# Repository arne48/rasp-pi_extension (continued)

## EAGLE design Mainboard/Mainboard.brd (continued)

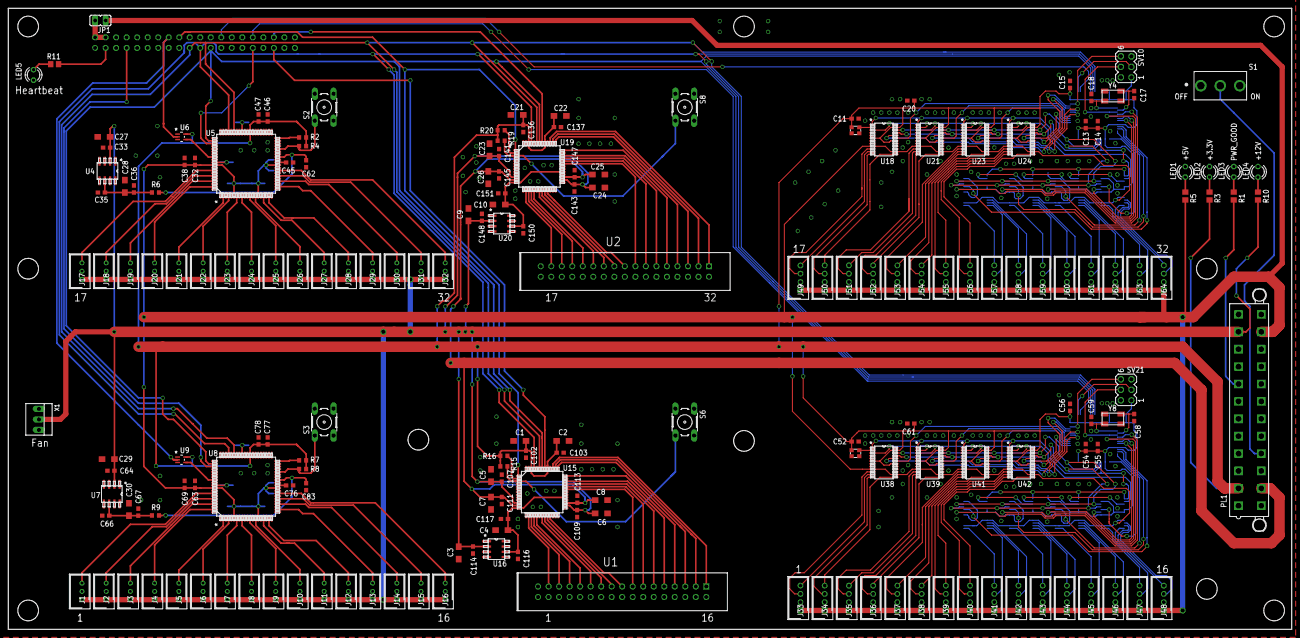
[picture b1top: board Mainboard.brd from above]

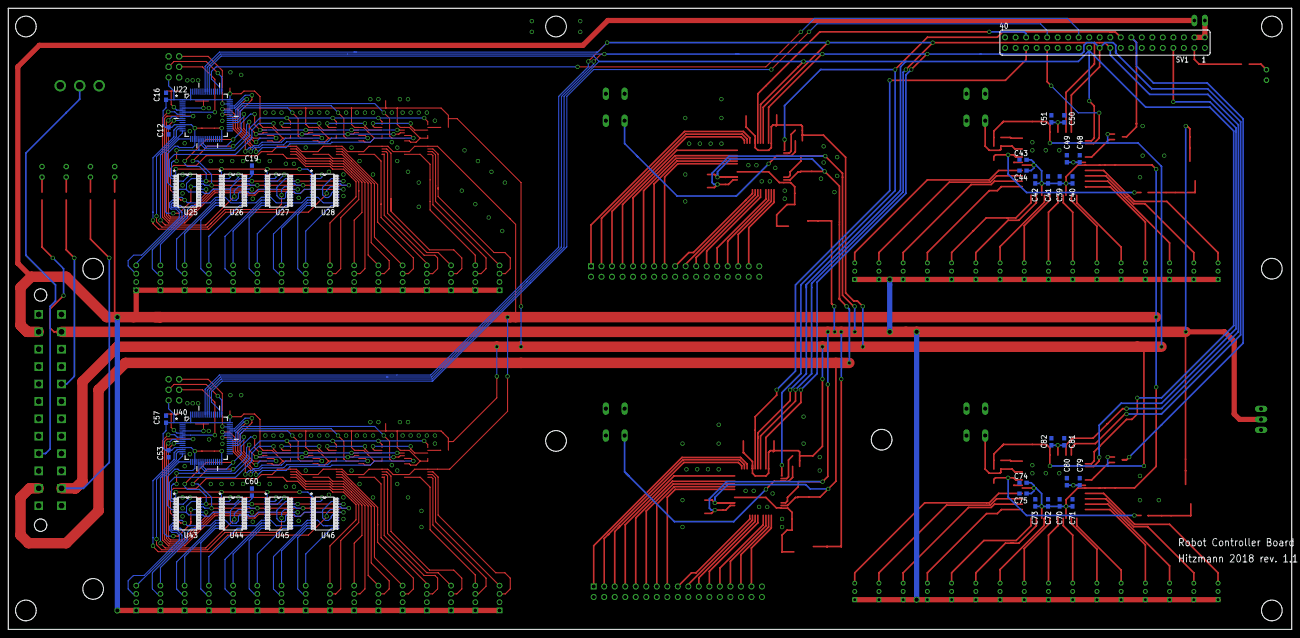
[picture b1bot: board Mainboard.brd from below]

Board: 2 copper layers, 310.0 x 150.0 mm, 225 parts (37 on the bottom side), 240 nets.

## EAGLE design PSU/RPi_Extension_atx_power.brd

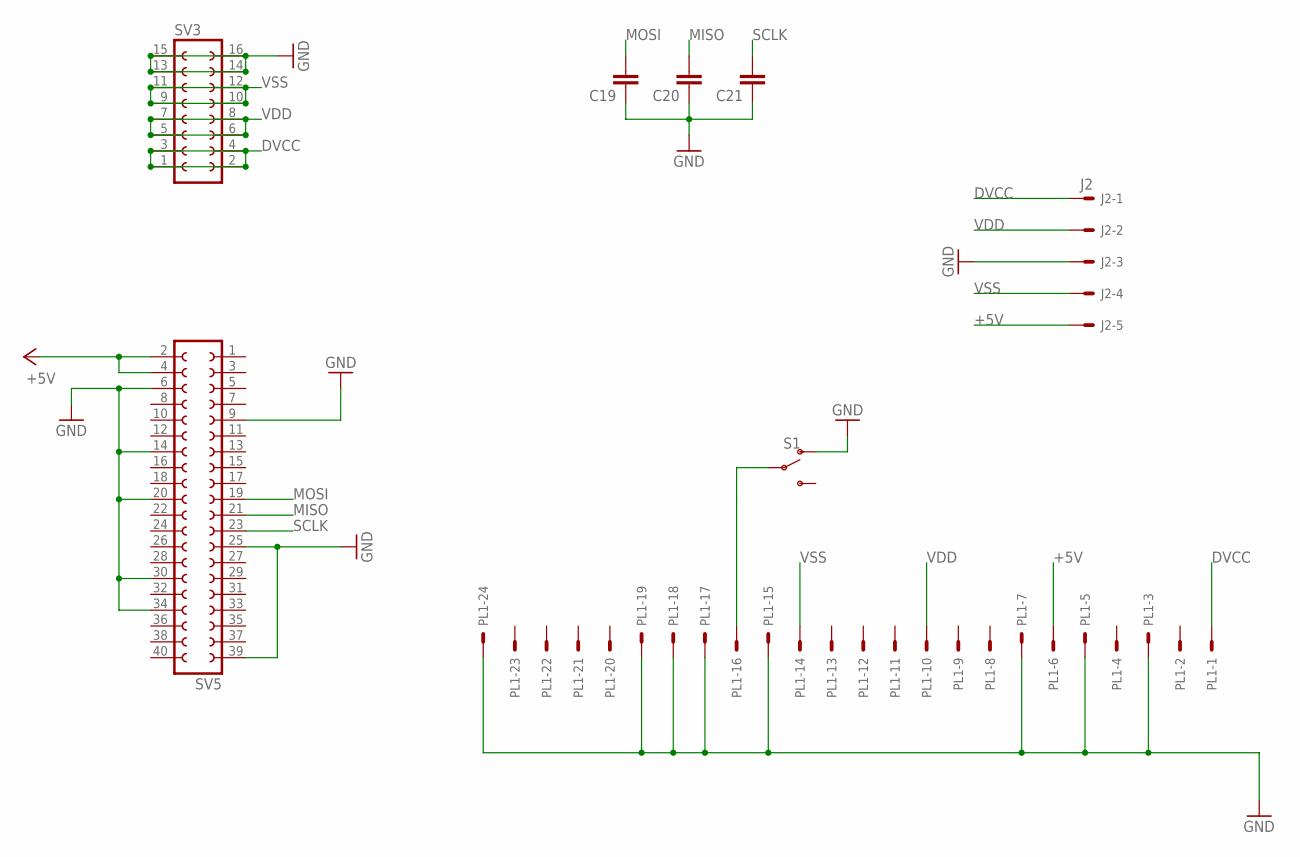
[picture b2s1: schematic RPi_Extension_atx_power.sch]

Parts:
C19, C20, C21: C-EUC0603; C0603
J2: J2; 6410-05
PL1: 555X-24V; 5566-24
S1: SWITCH-SPDT-PTH-11.6X4.0MM; SWITCH_SPDT_PTH_11.6X4.0MM
SV3: FE08-2
SV5: FE20-2

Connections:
+5V: J2.5, PL1.6, SV5.2, SV5.4
DVCC: J2.1, PL1.1, SV3.1, SV3.2, SV3.3, SV3.4
GND: C19.1, C20.1, C21.1, J2.3, PL1.3, PL1.5, PL1.7, PL1.15, PL1.17, PL1.18, PL1.19, PL1.24, S1.1 (O), SV3.13, SV3.14, SV3.15, SV3.16, SV5.6, SV5.9, SV5.14, SV5.20, SV5.25, SV5.30, SV5.34, SV5.39
MISO: C20.2, SV5.21
MOSI: C19.2, SV5.19
unnamed: PL1.16, S1.2
SCLK: C21.2, SV5.23
VDD: J2.2, PL1.10, SV3.5, SV3.6, SV3.7, SV3.8
VSS: J2.4, PL1.14, SV3.9, SV3.10, SV3.11, SV3.12

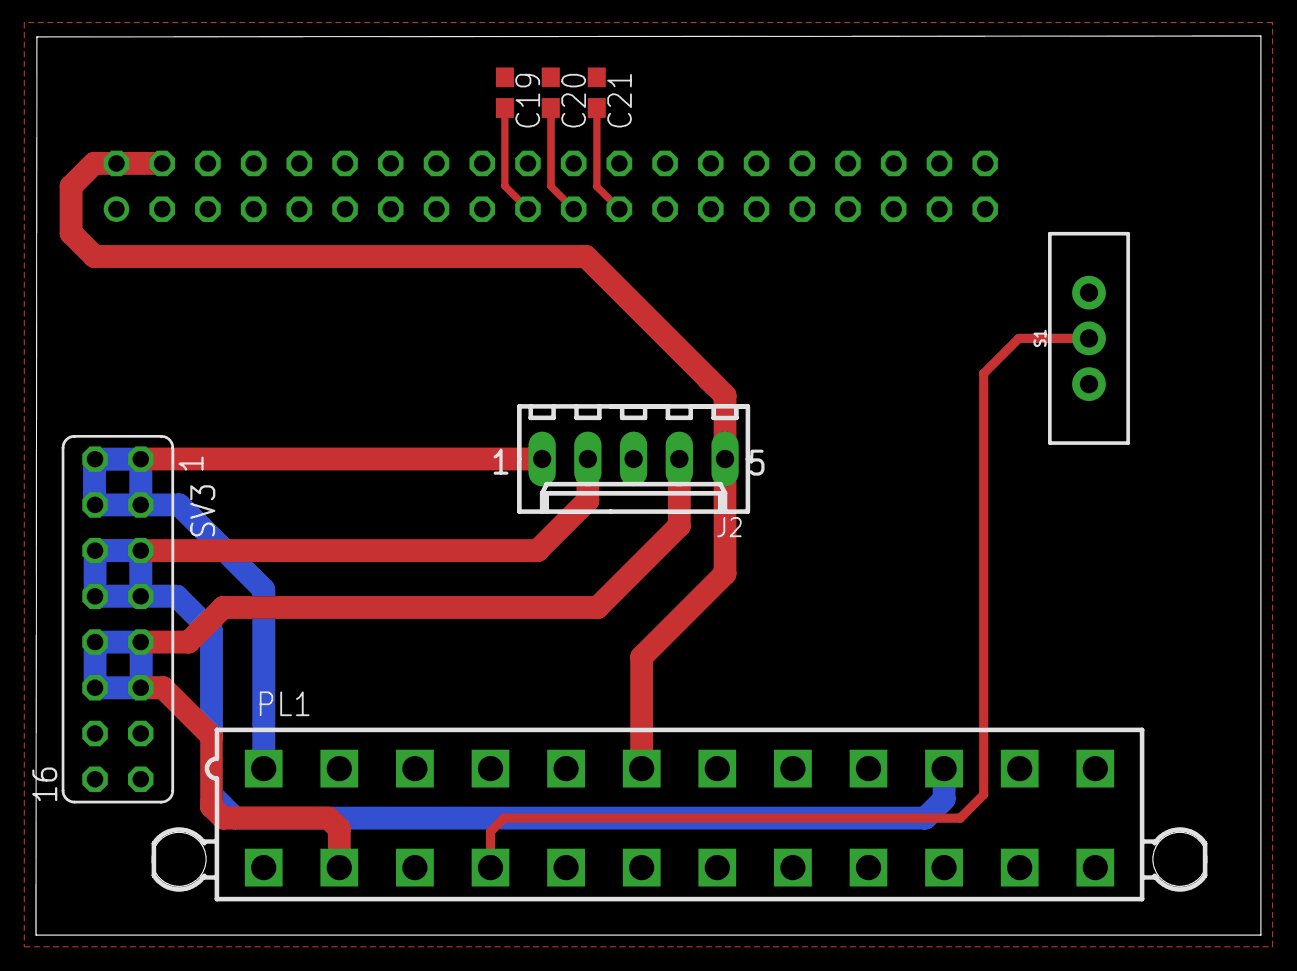
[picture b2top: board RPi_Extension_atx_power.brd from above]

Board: 2 copper layers, 68.0 x 50.0 mm, 8 parts (1 on the bottom side), 9 nets.

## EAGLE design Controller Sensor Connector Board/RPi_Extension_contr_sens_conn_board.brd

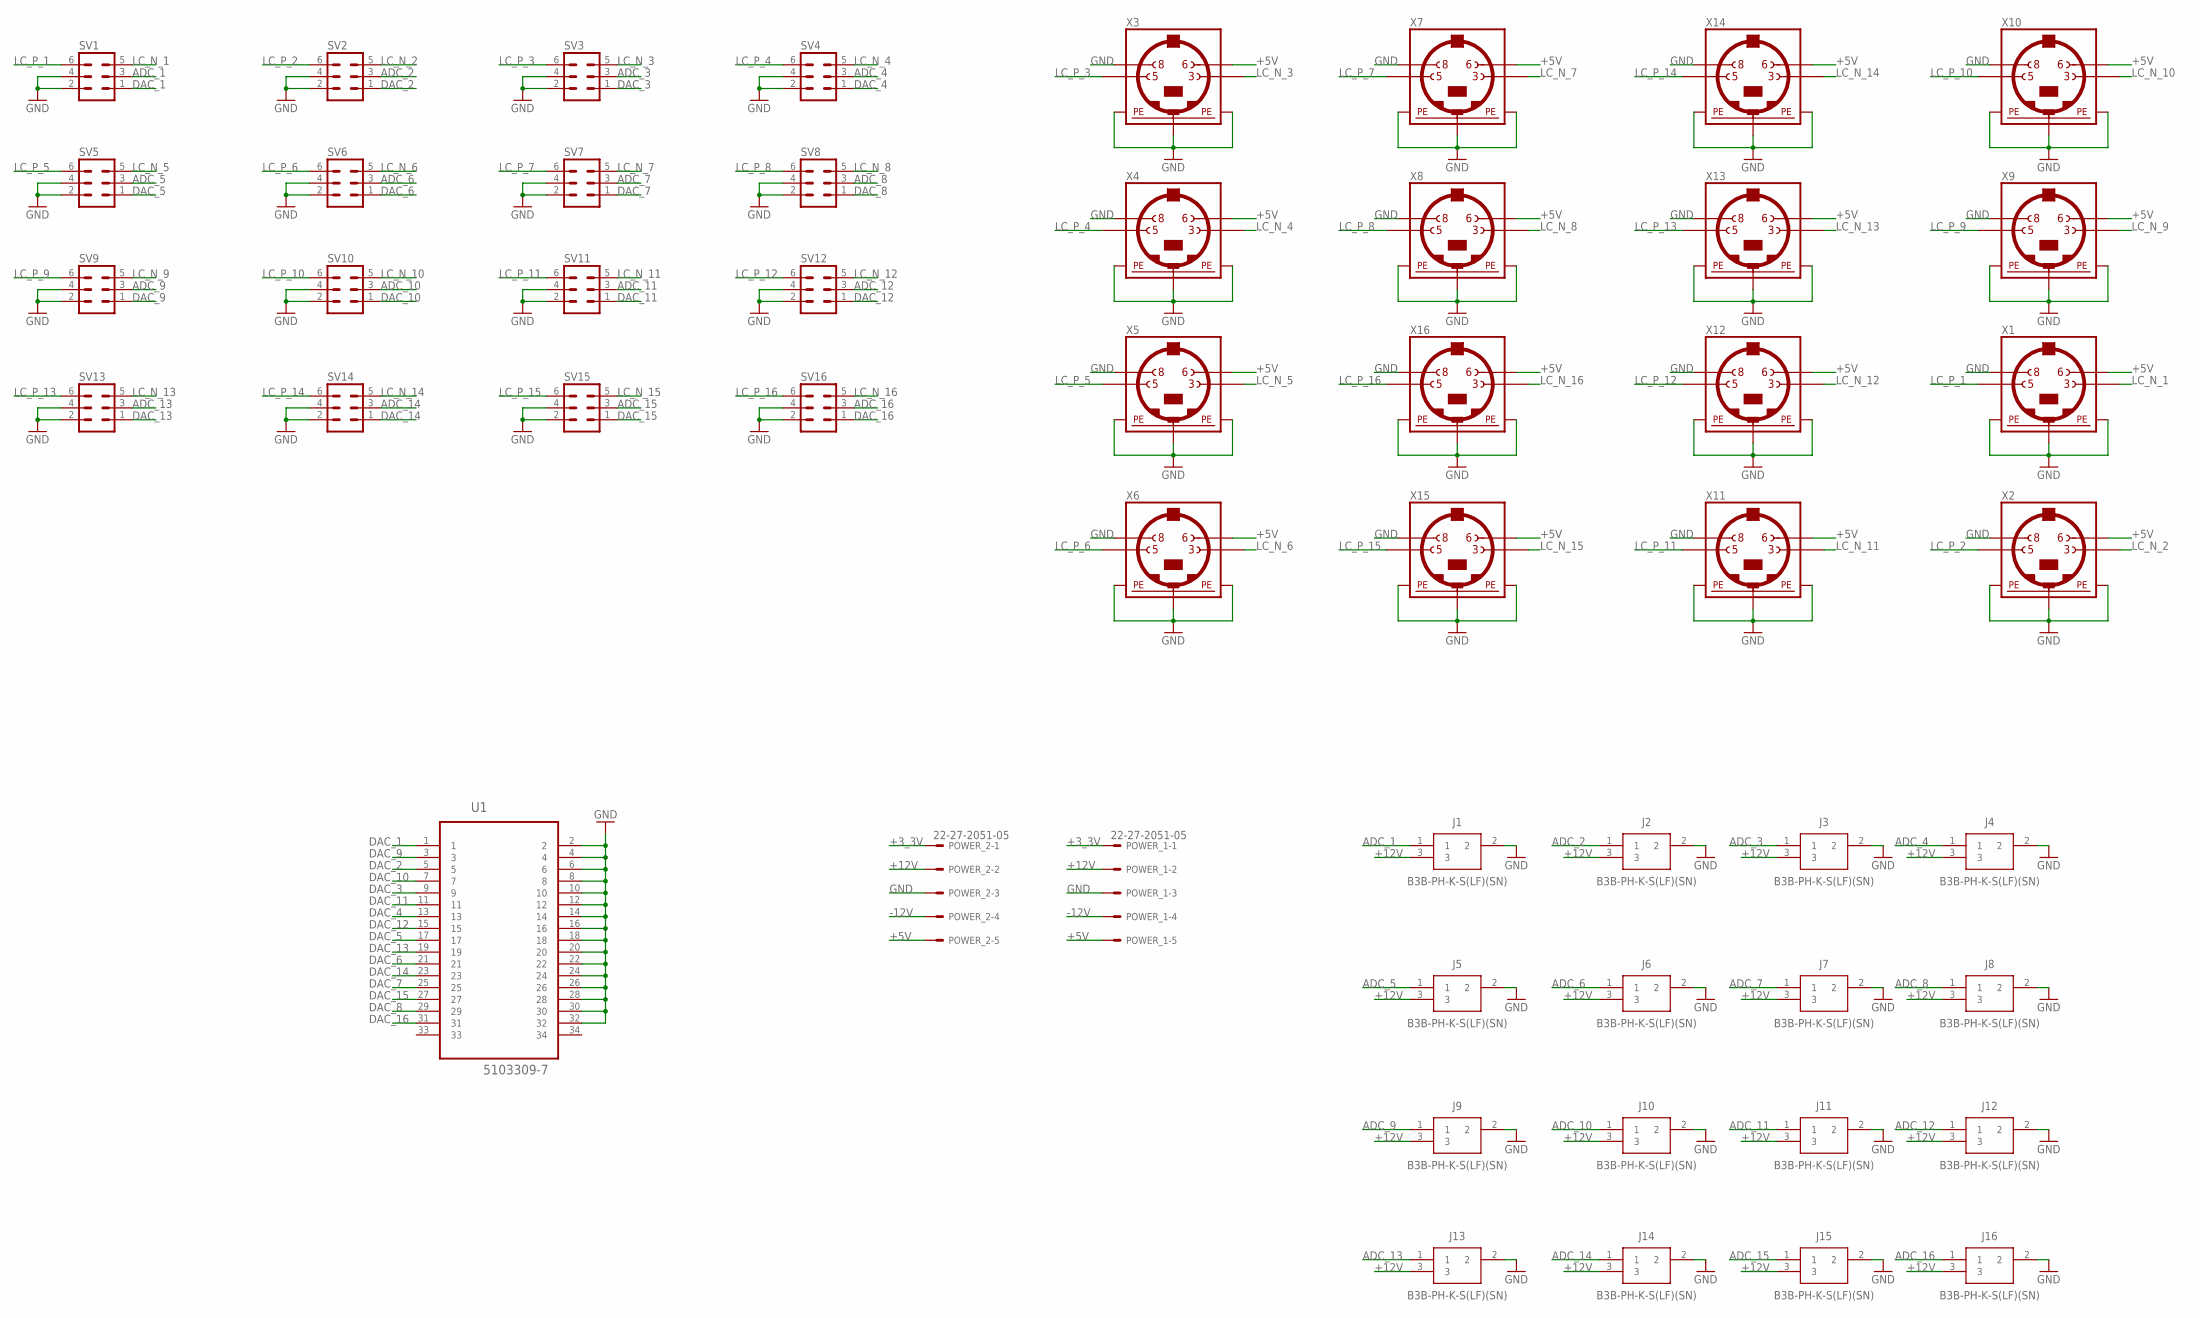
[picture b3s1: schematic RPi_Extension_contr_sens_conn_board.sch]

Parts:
J1, J2, J3, J4, J5, J6, J7, J8, J9, J10, J11, J12, J13, J14, J15, J16: B3B-PH-K-S(LF)(SN); SHDR3W50P0X200_1X3_790X450X600
POWER_1, POWER_2: 22-27-2051-05; 6410-05
SV1, SV2, SV3, SV4, SV5, SV6, SV7, SV8, SV9, SV10, SV11, SV12, SV13, SV14, SV15, SV16: MA03-2
U1: 5103309-7; TYCO_5103309-7
X1, X2, X3, X4, X5, X6, X7, X8, X9, X10, X11, X12, X13, X14, X15, X16: MINI_DIN_4; M_DIN4

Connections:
+3_3V: POWER_1.1, POWER_2.1
+5V: POWER_1.5, POWER_2.5, X1.6, X2.6, X3.6, X4.6, X5.6, X6.6, X7.6, X8.6, X9.6, X10.6, X11.6, X12.6, X13.6, X14.6, X15.6, X16.6
+12V: J1.3, J2.3, J3.3, J4.3, J5.3, J6.3, J7.3, J8.3, J9.3, J10.3, J11.3, J12.3, J13.3, J14.3, J15.3, J16.3, POWER_1.2, POWER_2.2
-12V: POWER_1.4, POWER_2.4
ADC_1: J1.1, SV1.3
ADC_2: J2.1, SV2.3
ADC_3: J3.1, SV3.3
ADC_4: J4.1, SV4.3
ADC_5: J5.1, SV5.3
ADC_6: J6.1, SV6.3
ADC_7: J7.1, SV7.3
ADC_8: J8.1, SV8.3
ADC_9: J9.1, SV9.3
ADC_10: J10.1, SV10.3
ADC_11: J11.1, SV11.3
ADC_12: J12.1, SV12.3
ADC_13: J13.1, SV13.3
ADC_14: J14.1, SV14.3
ADC_15: J15.1, SV15.3
ADC_16: J16.1, SV16.3
DAC_1: SV1.1, U1.1
DAC_2: SV2.1, U1.5
DAC_3: SV3.1, U1.9
DAC_4: SV4.1, U1.13
DAC_5: SV5.1, U1.17
DAC_6: SV6.1, U1.21
DAC_7: SV7.1, U1.25
DAC_8: SV8.1, U1.29
DAC_9: SV9.1, U1.3
DAC_10: SV10.1, U1.7
DAC_11: SV11.1, U1.11
DAC_12: SV12.1, U1.15
DAC_13: SV13.1, U1.19
DAC_14: SV14.1, U1.23
DAC_15: SV15.1, U1.27
DAC_16: SV16.1, U1.31
GND: J1.2, J2.2, J3.2, J4.2, J5.2, J6.2, J7.2, J8.2, J9.2, J10.2, J11.2, J12.2, J13.2, J14.2, J15.2, J16.2, POWER_1.3, POWER_2.3, SV1.2, SV1.4, SV2.2, SV2.4, SV3.2, SV3.4, SV4.2, SV4.4, SV5.2, SV5.4, SV6.2, SV6.4, SV7.2, SV7.4, SV8.2, SV8.4, SV9.2, SV9.4, SV10.2, SV10.4, SV11.2, SV11.4, SV12.2, SV12.4, SV13.2, SV13.4, SV14.2, SV14.4, SV15.2, SV15.4, SV16.2, SV16.4, U1.2, U1.4, U1.6, U1.8, U1.10, U1.12, U1.14, U1.16, U1.18, U1.20, U1.22, U1.24, U1.26, U1.28, U1.30, U1.32, X1.8, X1.SH1 (PE1), X1.SH2 (PE2), X1.SH3 (PE3), X2.8, X2.SH1 (PE1), X2.SH2 (PE2), X2.SH3 (PE3), X3.8, X3.SH1 (PE1), X3.SH2 (PE2), X3.SH3 (PE3), X4.8, X4.SH1 (PE1), X4.SH2 (PE2), X4.SH3 (PE3), X5.8, X5.SH1 (PE1), X5.SH2 (PE2), X5.SH3 (PE3), X6.8, X6.SH1 (PE1), X6.SH2 (PE2), X6.SH3 (PE3), X7.8, X7.SH1 (PE1), X7.SH2 (PE2), X7.SH3 (PE3), X8.8, X8.SH1 (PE1), X8.SH2 (PE2), X8.SH3 (PE3), X9.8, X9.SH1 (PE1), X9.SH2 (PE2), X9.SH3 (PE3), X10.8, X10.SH1 (PE1), X10.SH2 (PE2), X10.SH3 (PE3), X11.8, X11.SH1 (PE1), X11.SH2 (PE2), X11.SH3 (PE3), X12.8, X12.SH1 (PE1), X12.SH2 (PE2), X12.SH3 (PE3), X13.8, X13.SH1 (PE1), X13.SH2 (PE2), X13.SH3 (PE3), X14.8, X14.SH1 (PE1), X14.SH2 (PE2), X14.SH3 (PE3), X15.8, X15.SH1 (PE1), X15.SH2 (PE2), X15.SH3 (PE3), X16.8, X16.SH1 (PE1), X16.SH2 (PE2), X16.SH3 (PE3)
LC_N_1: SV1.5, X1.3
LC_N_2: SV2.5, X2.3
LC_N_3: SV3.5, X3.3
LC_N_4: SV4.5, X4.3
LC_N_5: SV5.5, X5.3
LC_N_6: SV6.5, X6.3
LC_N_7: SV7.5, X7.3
LC_N_8: SV8.5, X8.3
LC_N_9: SV9.5, X9.3
LC_N_10: SV10.5, X10.3
LC_N_11: SV11.5, X11.3
LC_N_12: SV12.5, X12.3
LC_N_13: SV13.5, X13.3
LC_N_14: SV14.5, X14.3
LC_N_15: SV15.5, X15.3
LC_N_16: SV16.5, X16.3
LC_P_1: SV1.6, X1.5
LC_P_2: SV2.6, X2.5
LC_P_3: SV3.6, X3.5
LC_P_4: SV4.6, X4.5
LC_P_5: SV5.6, X5.5
LC_P_6: SV6.6, X6.5
LC_P_7: SV7.6, X7.5
LC_P_8: SV8.6, X8.5
LC_P_9: SV9.6, X9.5
LC_P_10: SV10.6, X10.5
LC_P_11: SV11.6, X11.5
LC_P_12: SV12.6, X12.5
LC_P_13: SV13.6, X13.5
LC_P_14: SV14.6, X14.5
LC_P_15: SV15.6, X15.5
LC_P_16: SV16.6, X16.5

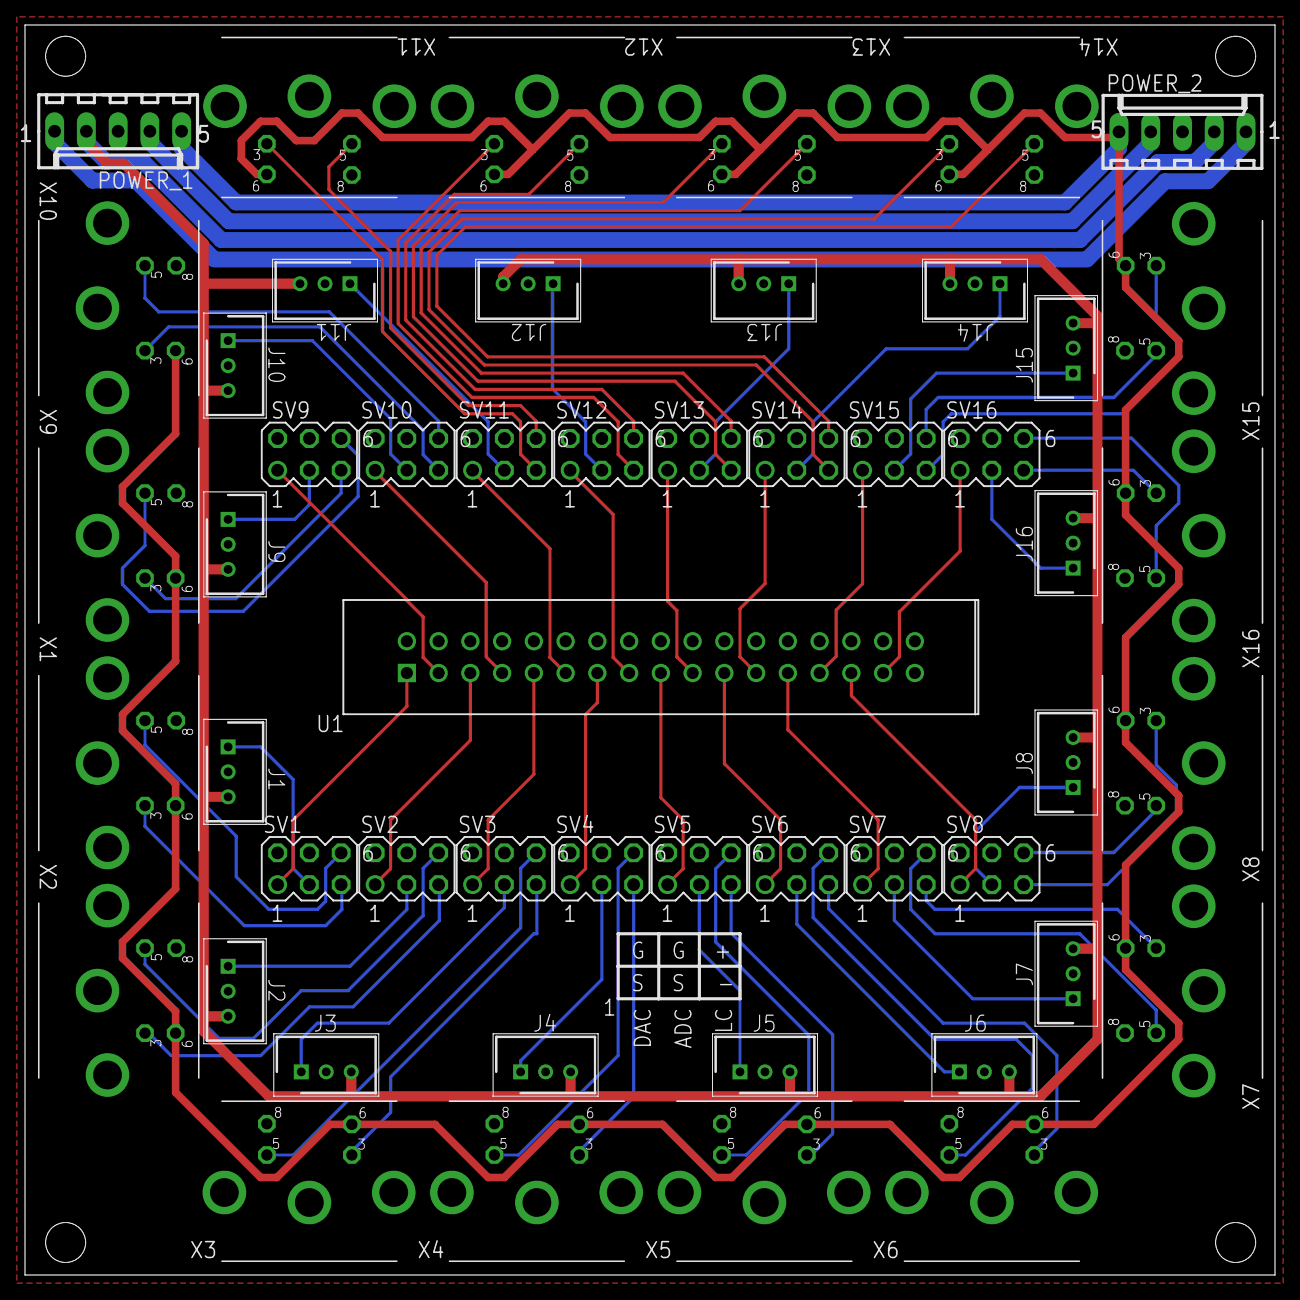
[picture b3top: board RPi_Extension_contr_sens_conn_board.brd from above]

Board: 2 copper layers, 100.0 x 100.0 mm, 51 parts (0 on the bottom side), 69 nets.

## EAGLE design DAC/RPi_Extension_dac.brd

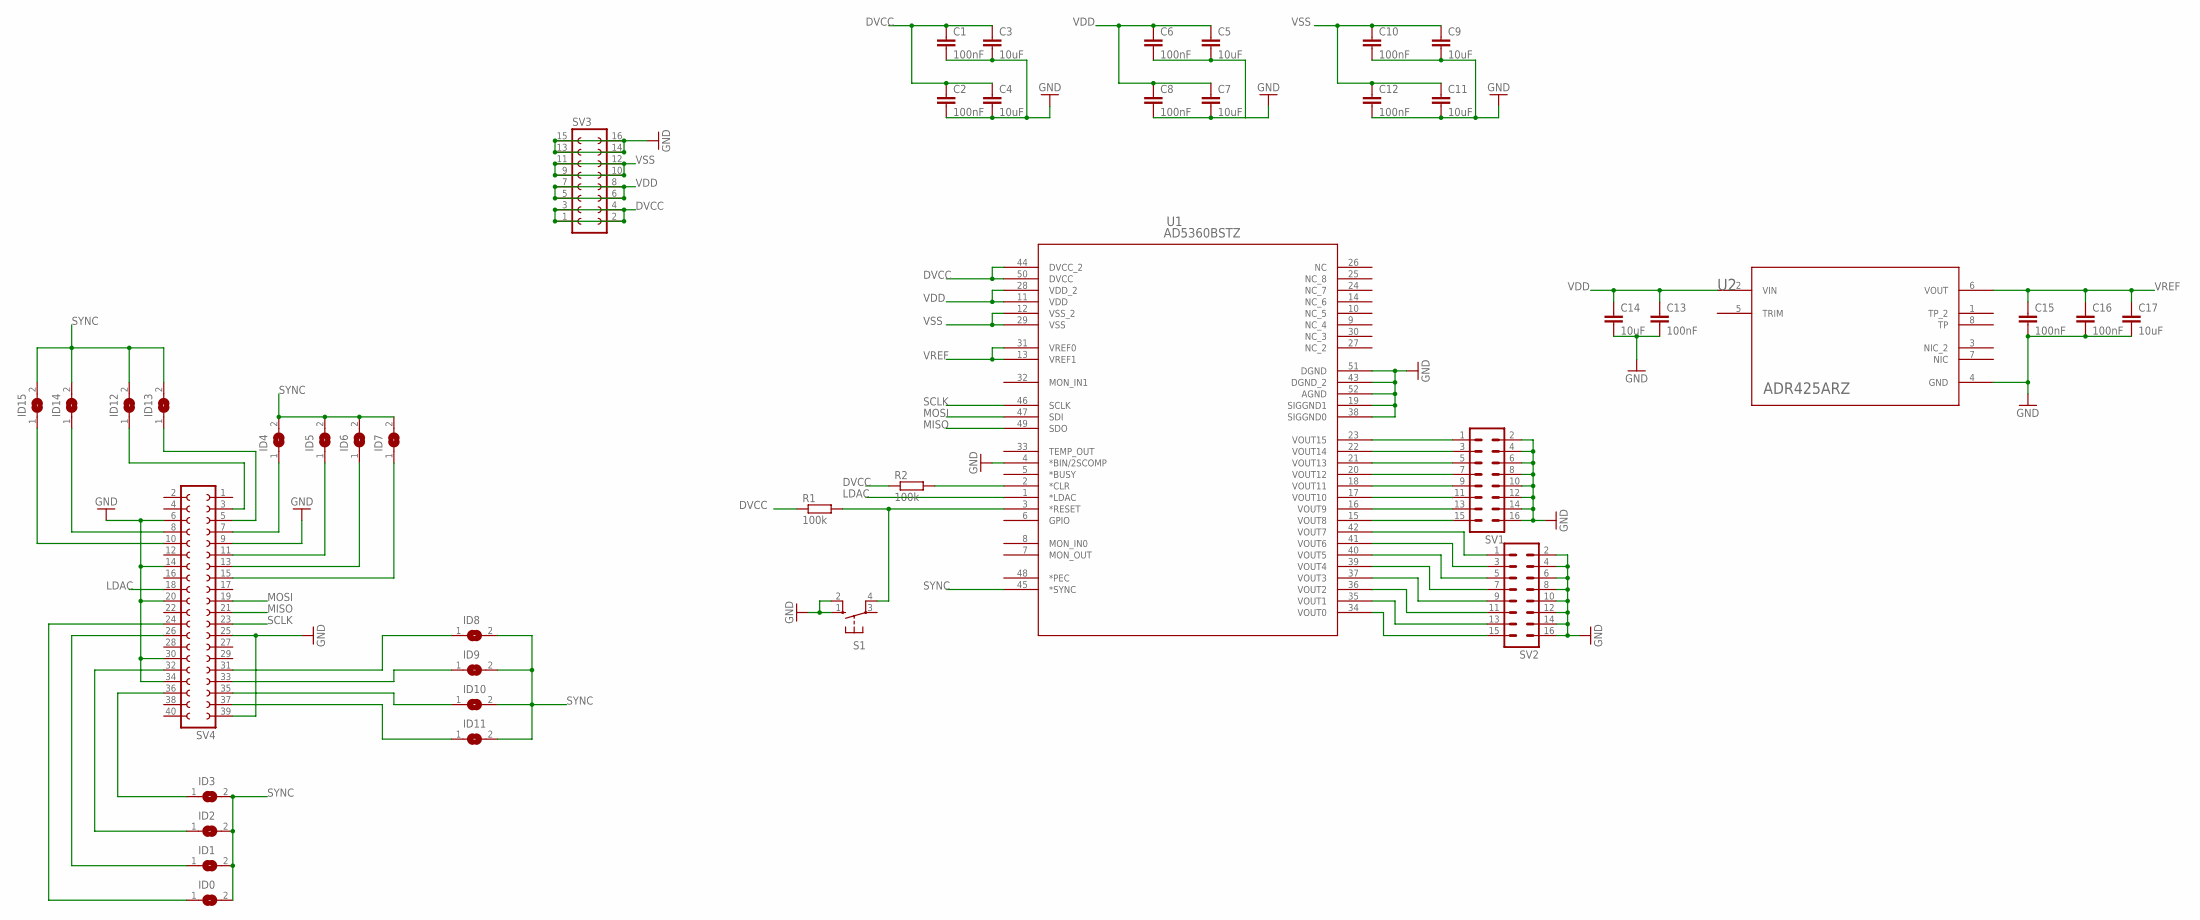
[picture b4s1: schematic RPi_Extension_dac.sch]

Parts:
C1, C2, C6, C8, C10, C12, C13, C15, C16: 100nF; C0603
C3, C4, C5, C7, C9, C11, C14, C17: 10uF; C1206
ID0, ID1, ID2, ID3, ID4, ID5, ID6, ID7, ID8, ID9, ID10, ID11, ID12, ID13, ID14, ID15: SJ
R1, R2: 100k; R0603
S1: 10-XX; B3F-10XX
SV1, SV2: MA08-2W
SV3: FE08-2
SV4: FE20-2
U1: AD5360BSTZ; ST_52
U2: ADR425ARZ; R_8

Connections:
DVCC: C1.1, C2.1, C3.1, C4.1, R1.1, R2.1, SV3.1, SV3.2, SV3.3, SV3.4, U1.44 (DVCC_2), U1.50 (DVCC)
GND: C1.2, C2.2, C3.2, C4.2, C5.2, C6.2, C7.2, C8.2, C9.2, C10.2, C11.2, C12.2, C13.2, C14.2, C15.2, C16.2, C17.2, S1.1 (S), S1.2 (S1), SV1.2, SV1.4, SV1.6, SV1.8, SV1.10, SV1.12, SV1.14, SV1.16, SV2.2, SV2.4, SV2.6, SV2.8, SV2.10, SV2.12, SV2.14, SV2.16, SV3.13, SV3.14, SV3.15, SV3.16, SV4.6, SV4.9, SV4.14, SV4.20, SV4.25, SV4.30, SV4.34, SV4.39, U1.4 (*BIN/2SCOMP), U1.19 (SIGGND1), U1.38 (SIGGND0), U1.43 (DGND_2), U1.51 (DGND), U1.52 (AGND), U2.4 (GND)
LDAC: SV4.18, U1.1 (*LDAC)
MISO: SV4.21, U1.49 (SDO)
MOSI: SV4.19, U1.47 (SDI)
unnamed: R2.2, U1.2 (*CLR)
unnamed: SV1.1, U1.23 (VOUT15)
unnamed: SV1.3, U1.22 (VOUT14)
unnamed: SV1.5, U1.21 (VOUT13)
unnamed: SV1.7, U1.20 (VOUT12)
unnamed: SV1.9, U1.18 (VOUT11)
unnamed: SV1.11, U1.17 (VOUT10)
unnamed: SV1.13, U1.16 (VOUT9)
unnamed: SV1.15, U1.15 (VOUT8)
unnamed: SV2.1, U1.42 (VOUT7)
unnamed: SV2.3, U1.41 (VOUT6)
unnamed: SV2.5, U1.40 (VOUT5)
unnamed: SV2.7, U1.39 (VOUT4)
unnamed: SV2.9, U1.37 (VOUT3)
unnamed: SV2.11, U1.36 (VOUT2)
unnamed: SV2.13, U1.35 (VOUT1)
unnamed: SV2.15, U1.34 (VOUT0)
unnamed: R1.2, S1.4 (P1), U1.3 (*RESET)
unnamed: ID8.1, SV4.31
unnamed: ID3.1, SV4.36
unnamed: ID4.1, SV4.7
unnamed: ID2.1, SV4.32
unnamed: ID1.1, SV4.26
unnamed: ID0.1, SV4.24
unnamed: ID5.1, SV4.11
unnamed: ID6.1, SV4.13
unnamed: ID7.1, SV4.15
unnamed: ID9.1, SV4.33
unnamed: ID10.1, SV4.35
unnamed: ID11.1, SV4.37
unnamed: ID12.1, SV4.3
unnamed: ID13.1, SV4.5
unnamed: ID14.1, SV4.8
unnamed: ID15.1, SV4.10
SCLK: SV4.23, U1.46 (SCLK)
SYNC: ID0.2, ID1.2, ID2.2, ID3.2, ID4.2, ID5.2, ID6.2, ID7.2, ID8.2, ID9.2, ID10.2, ID11.2, ID12.2, ID13.2, ID14.2, ID15.2, U1.45 (*SYNC)
VDD: C5.1, C6.1, C7.1, C8.1, C13.1, C14.1, SV3.5, SV3.6, SV3.7, SV3.8, U1.11 (VDD), U1.28 (VDD_2), U2.2 (VIN)
VREF: C15.1, C16.1, C17.1, U1.13 (VREF1), U1.31 (VREF0), U2.6 (VOUT)
VSS: C9.1, C10.1, C11.1, C12.1, SV3.9, SV3.10, SV3.11, SV3.12, U1.12 (VSS_2), U1.29 (VSS)

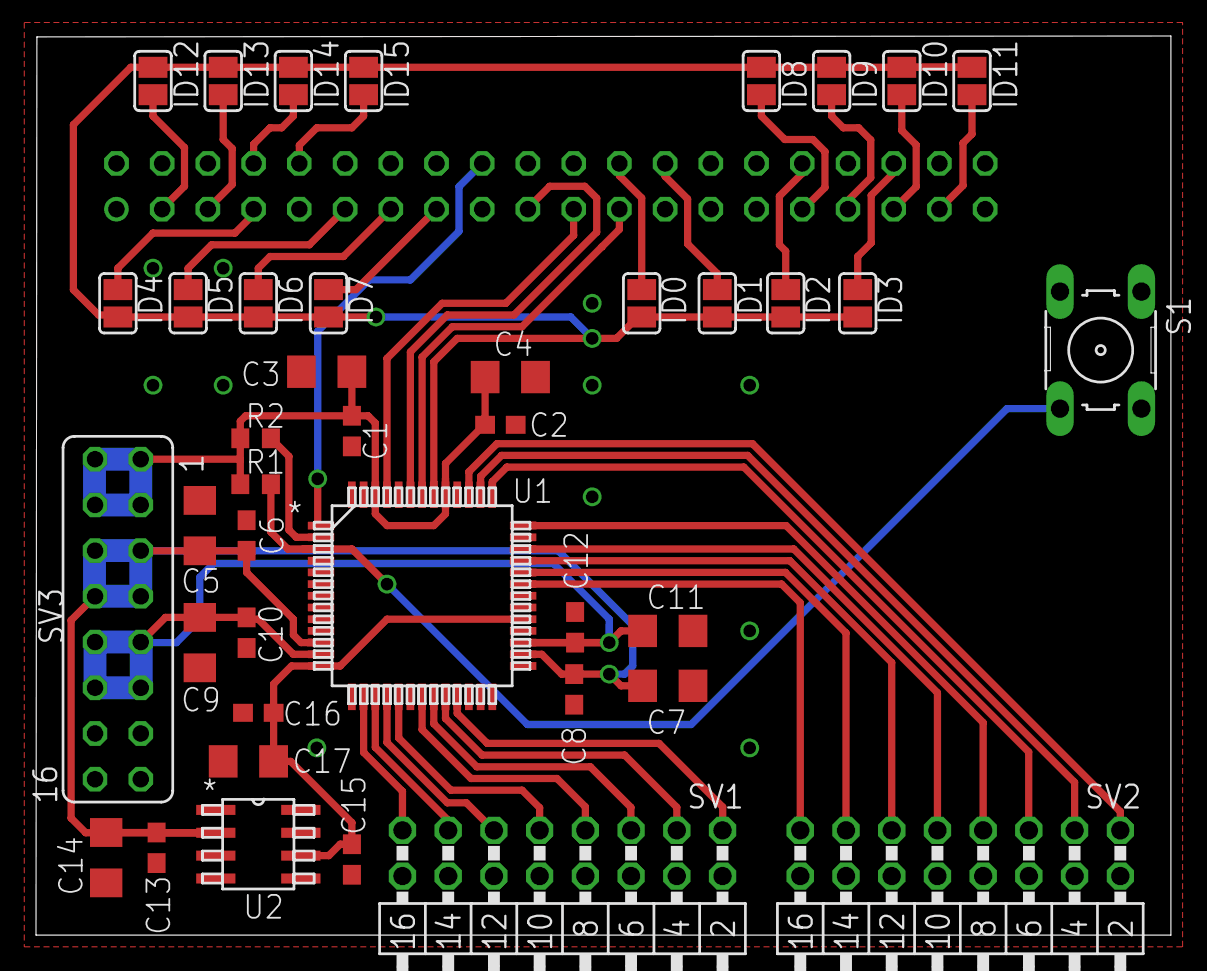
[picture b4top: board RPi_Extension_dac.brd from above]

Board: 2 copper layers, 63.0 x 50.0 mm, 42 parts (1 on the bottom side), 44 nets.

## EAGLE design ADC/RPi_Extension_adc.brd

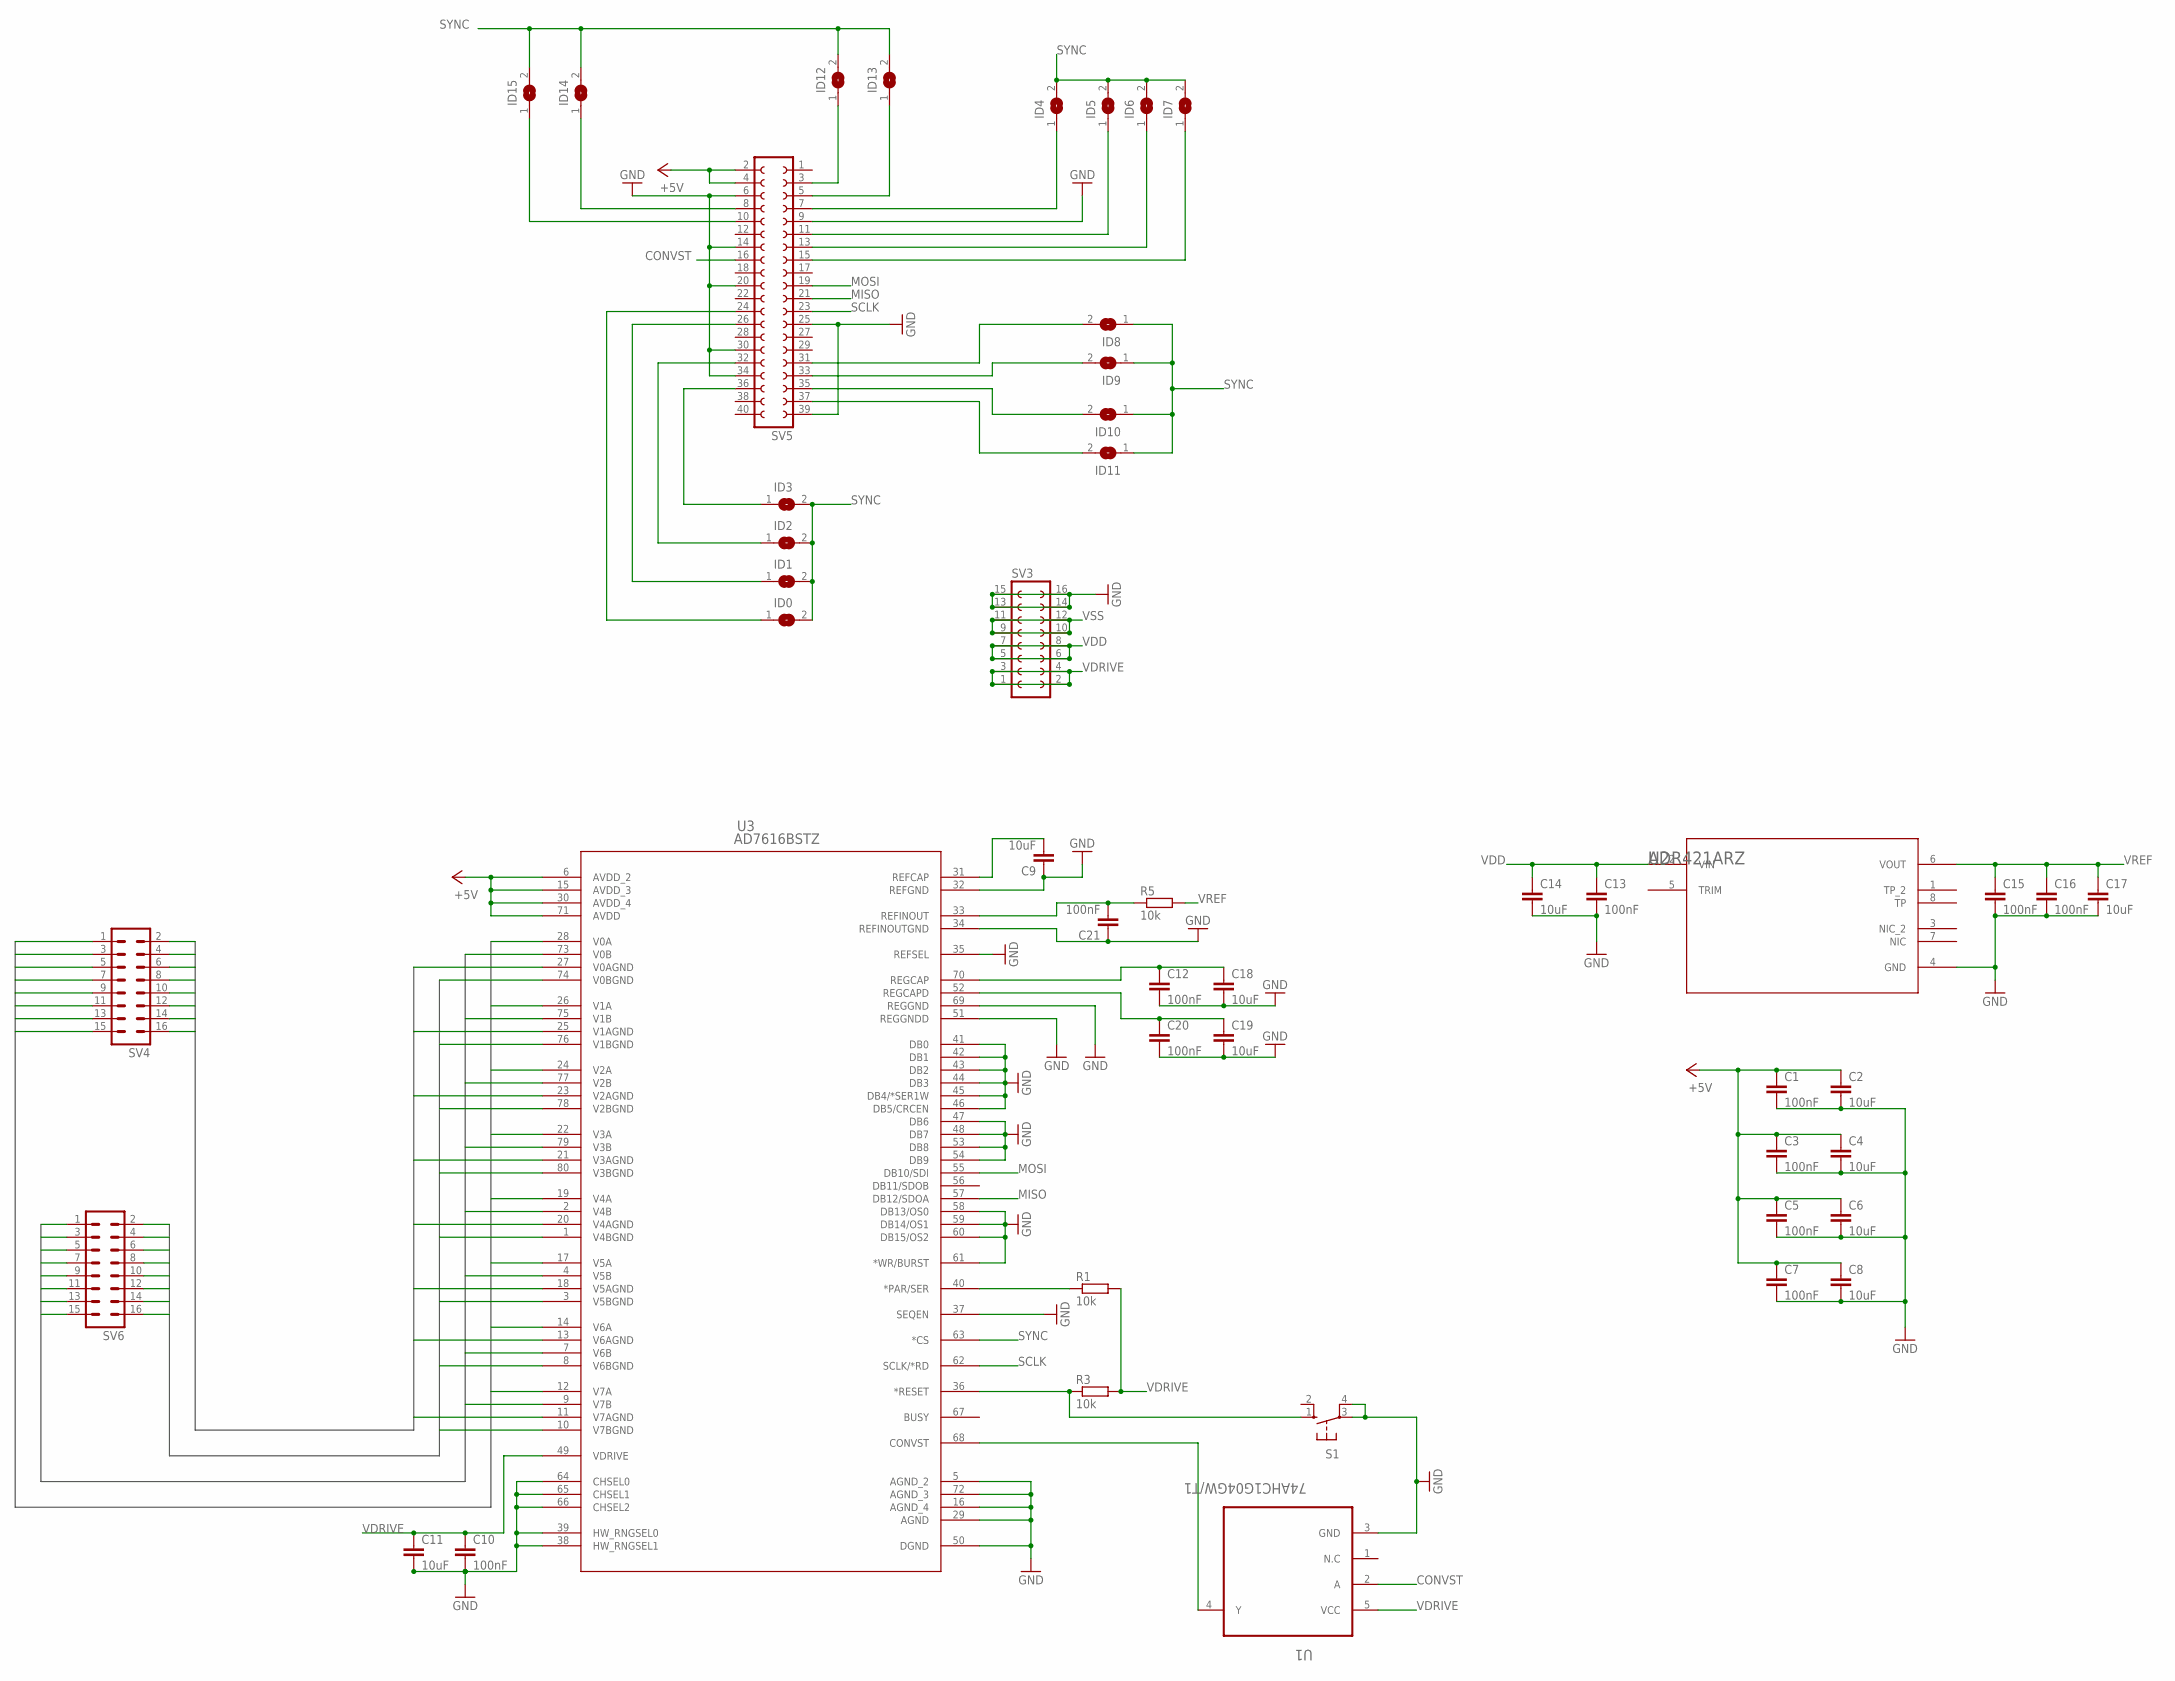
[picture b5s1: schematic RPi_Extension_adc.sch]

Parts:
C1, C3, C5, C7, C10, C12, C13, C15, C16, C20, C21: 100nF; C0603
C2, C4, C6, C8, C9, C11, C18, C19: 10uF; C0603
C14, C17: 10uF; C1206
ID0, ID1, ID2, ID3, ID4, ID5, ID6, ID7, ID8, ID9, ID10, ID11, ID12, ID13, ID14, ID15: SJ
R1, R3, R5: 10k; R0603
S1: 10-XX; B3F-10XX
SV3: FE08-2
SV4, SV6: MA08-2W
SV5: FE20-2
U1: 74AHC1G04GW/T1; SOT65P210X110-5N
U2: ADR421ARZ; R_8
U3: AD7616BSTZ; ST_80_2

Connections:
+5V: C1.1, C2.1, C3.1, C4.1, C5.1, C6.1, C7.1, C8.1, SV5.2, SV5.4, U3.6 (AVDD_2), U3.15 (AVDD_3), U3.30 (AVDD_4), U3.71 (AVDD)
CONVST: SV5.16, U1.2 (A)
GND: C1.2, C2.2, C3.2, C4.2, C5.2, C6.2, C7.2, C8.2, C9.1, C10.2, C11.2, C12.2, C13.2, C14.2, C15.2, C16.2, C17.2, C18.2, C19.2, C20.2, C21.1, S1.3, S1.4 (P1), SV3.13, SV3.14, SV3.15, SV3.16, SV5.6, SV5.9, SV5.14, SV5.20, SV5.25, SV5.30, SV5.34, SV5.39, U1.3 (GND), U2.4 (GND), U3.5 (AGND_2), U3.16 (AGND_4), U3.29 (AGND), U3.32 (REFGND), U3.34 (REFINOUTGND), U3.35 (REFSEL), U3.37 (SEQEN), U3.38 (HW_RNGSEL1), U3.39 (HW_RNGSEL0), U3.41 (DB0), U3.42 (DB1), U3.43 (DB2), U3.44 (DB3), U3.45 (DB4/*SER1W), U3.46 (DB5/CRCEN), U3.47 (DB6), U3.48 (DB7), U3.50 (DGND), U3.51 (REGGNDD), U3.53 (DB8), U3.54 (DB9), U3.58 (DB13/OS0), U3.59 (DB14/OS1), U3.60 (DB15/OS2), U3.61 (*WR/BURST), U3.64 (CHSEL0), U3.65 (CHSEL1), U3.66 (CHSEL2), U3.69 (REGGND), U3.72 (AGND_3)
MISO: SV5.21, U3.57 (DB12/SDOA)
MOSI: SV5.19, U3.55 (DB10/SDI)
unnamed: C12.1, C18.1, U3.70 (REGCAP)
unnamed: C9.2, U3.31 (REFCAP)
unnamed: U1.4 (Y), U3.68 (CONVST)
unnamed: ID12.1, SV5.3
unnamed: R1.1, U3.40 (*PAR/SER)
unnamed: R3.1, S1.1 (S), U3.36 (*RESET)
unnamed: ID13.1, SV5.5
unnamed: ID14.1, SV5.8
unnamed: C21.2, R5.1, U3.33 (REFINOUT)
unnamed: ID15.1, SV5.10
unnamed: ID8.2, SV5.31
unnamed: ID9.2, SV5.33
unnamed: ID10.2, SV5.35
unnamed: ID11.2, SV5.37
unnamed: C19.1, C20.1, U3.52 (REGCAPD)
unnamed: ID3.1, SV5.36
unnamed: ID4.1, SV5.7
unnamed: ID2.1, SV5.32
unnamed: ID1.1, SV5.26
unnamed: ID0.1, SV5.24
unnamed: ID5.1, SV5.11
unnamed: ID6.1, SV5.13
unnamed: ID7.1, SV5.15
SCLK: SV5.23, U3.62 (SCLK/*RD)
SYNC: ID0.2, ID1.2, ID2.2, ID3.2, ID4.2, ID5.2, ID6.2, ID7.2, ID8.1, ID9.1, ID10.1, ID11.1, ID12.2, ID13.2, ID14.2, ID15.2, U3.63 (*CS)
VA_GND0: SV4.2, U3.27 (V0AGND)
VA_GND1: SV4.4, U3.25 (V1AGND)
VA_GND2: SV4.6, U3.23 (V2AGND)
VA_GND3: SV4.8, U3.21 (V3AGND)
VA_GND4: SV4.10, U3.20 (V4AGND)
VA_GND5: SV4.12, U3.18 (V5AGND)
VA_GND6: SV4.14, U3.13 (V6AGND)
VA_GND7: SV4.16, U3.11 (V7AGND)
VA_IN0: SV4.1, U3.28 (V0A)
VA_IN1: SV4.3, U3.26 (V1A)
VA_IN2: SV4.5, U3.24 (V2A)
VA_IN3: SV4.7, U3.22 (V3A)
VA_IN4: SV4.9, U3.19 (V4A)
VA_IN5: SV4.11, U3.17 (V5A)
VA_IN6: SV4.13, U3.14 (V6A)
VA_IN7: SV4.15, U3.12 (V7A)
VB_GND0: SV6.16, U3.74 (V0BGND)
VB_GND1: SV6.14, U3.76 (V1BGND)
VB_GND2: SV6.12, U3.78 (V2BGND)
VB_GND3: SV6.10, U3.80 (V3BGND)
VB_GND4: SV6.8, U3.1 (V4BGND)
VB_GND5: SV6.6, U3.3 (V5BGND)
VB_GND6: SV6.4, U3.8 (V6BGND)
VB_GND7: SV6.2, U3.10 (V7BGND)
VB_IN0: SV6.15, U3.73 (V0B)
VB_IN1: SV6.13, U3.75 (V1B)
VB_IN2: SV6.11, U3.77 (V2B)
VB_IN3: SV6.9, U3.79 (V3B)
VB_IN4: SV6.7, U3.2 (V4B)
VB_IN5: SV6.5, U3.4 (V5B)
VB_IN6: SV6.3, U3.7 (V6B)
VB_IN7: SV6.1, U3.9 (V7B)
VDD: C13.1, C14.1, SV3.5, SV3.6, SV3.7, SV3.8, U2.2 (VIN)
VDRIVE: C10.1, C11.1, R1.2, R3.2, SV3.1, SV3.2, SV3.3, SV3.4, U1.5 (VCC), U3.49 (VDRIVE)
VREF: C15.1, C16.1, C17.1, R5.2, U2.6 (VOUT)
VSS: SV3.9, SV3.10, SV3.11, SV3.12
